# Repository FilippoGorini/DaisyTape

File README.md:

# DaisyTape

## Author

<!-- Insert Your Name Here -->

## Description

<!-- Describe your example here -->

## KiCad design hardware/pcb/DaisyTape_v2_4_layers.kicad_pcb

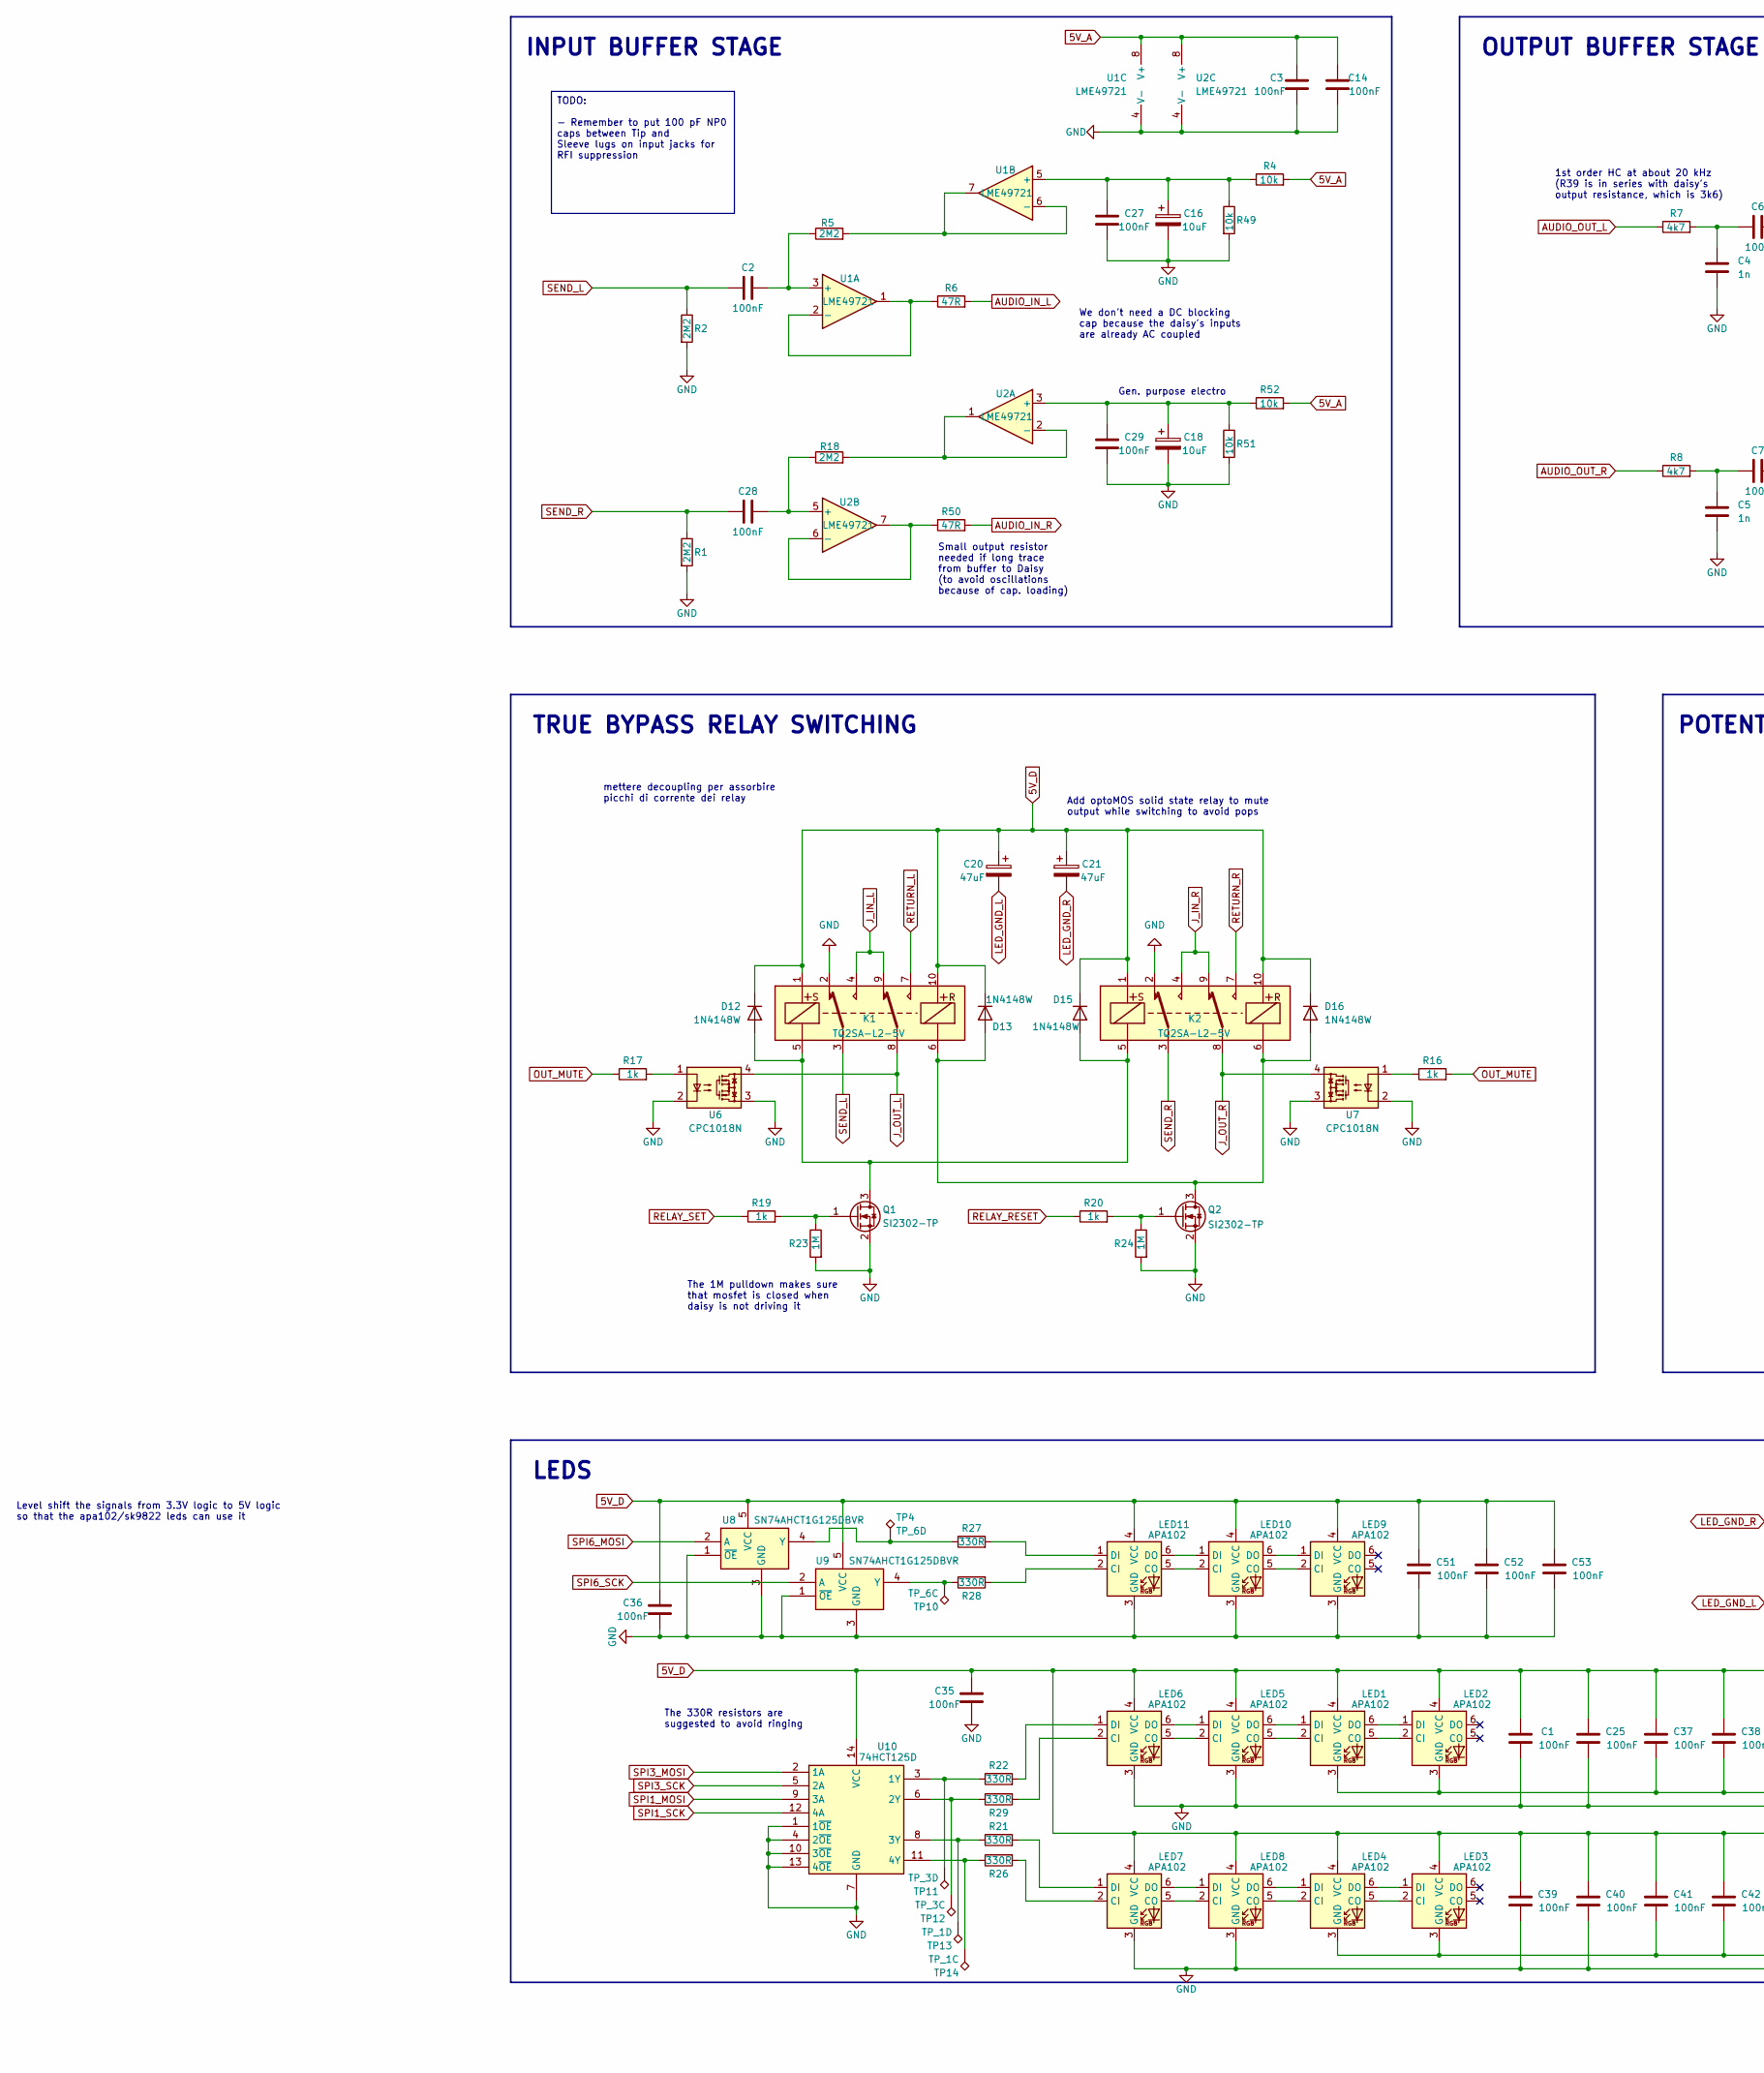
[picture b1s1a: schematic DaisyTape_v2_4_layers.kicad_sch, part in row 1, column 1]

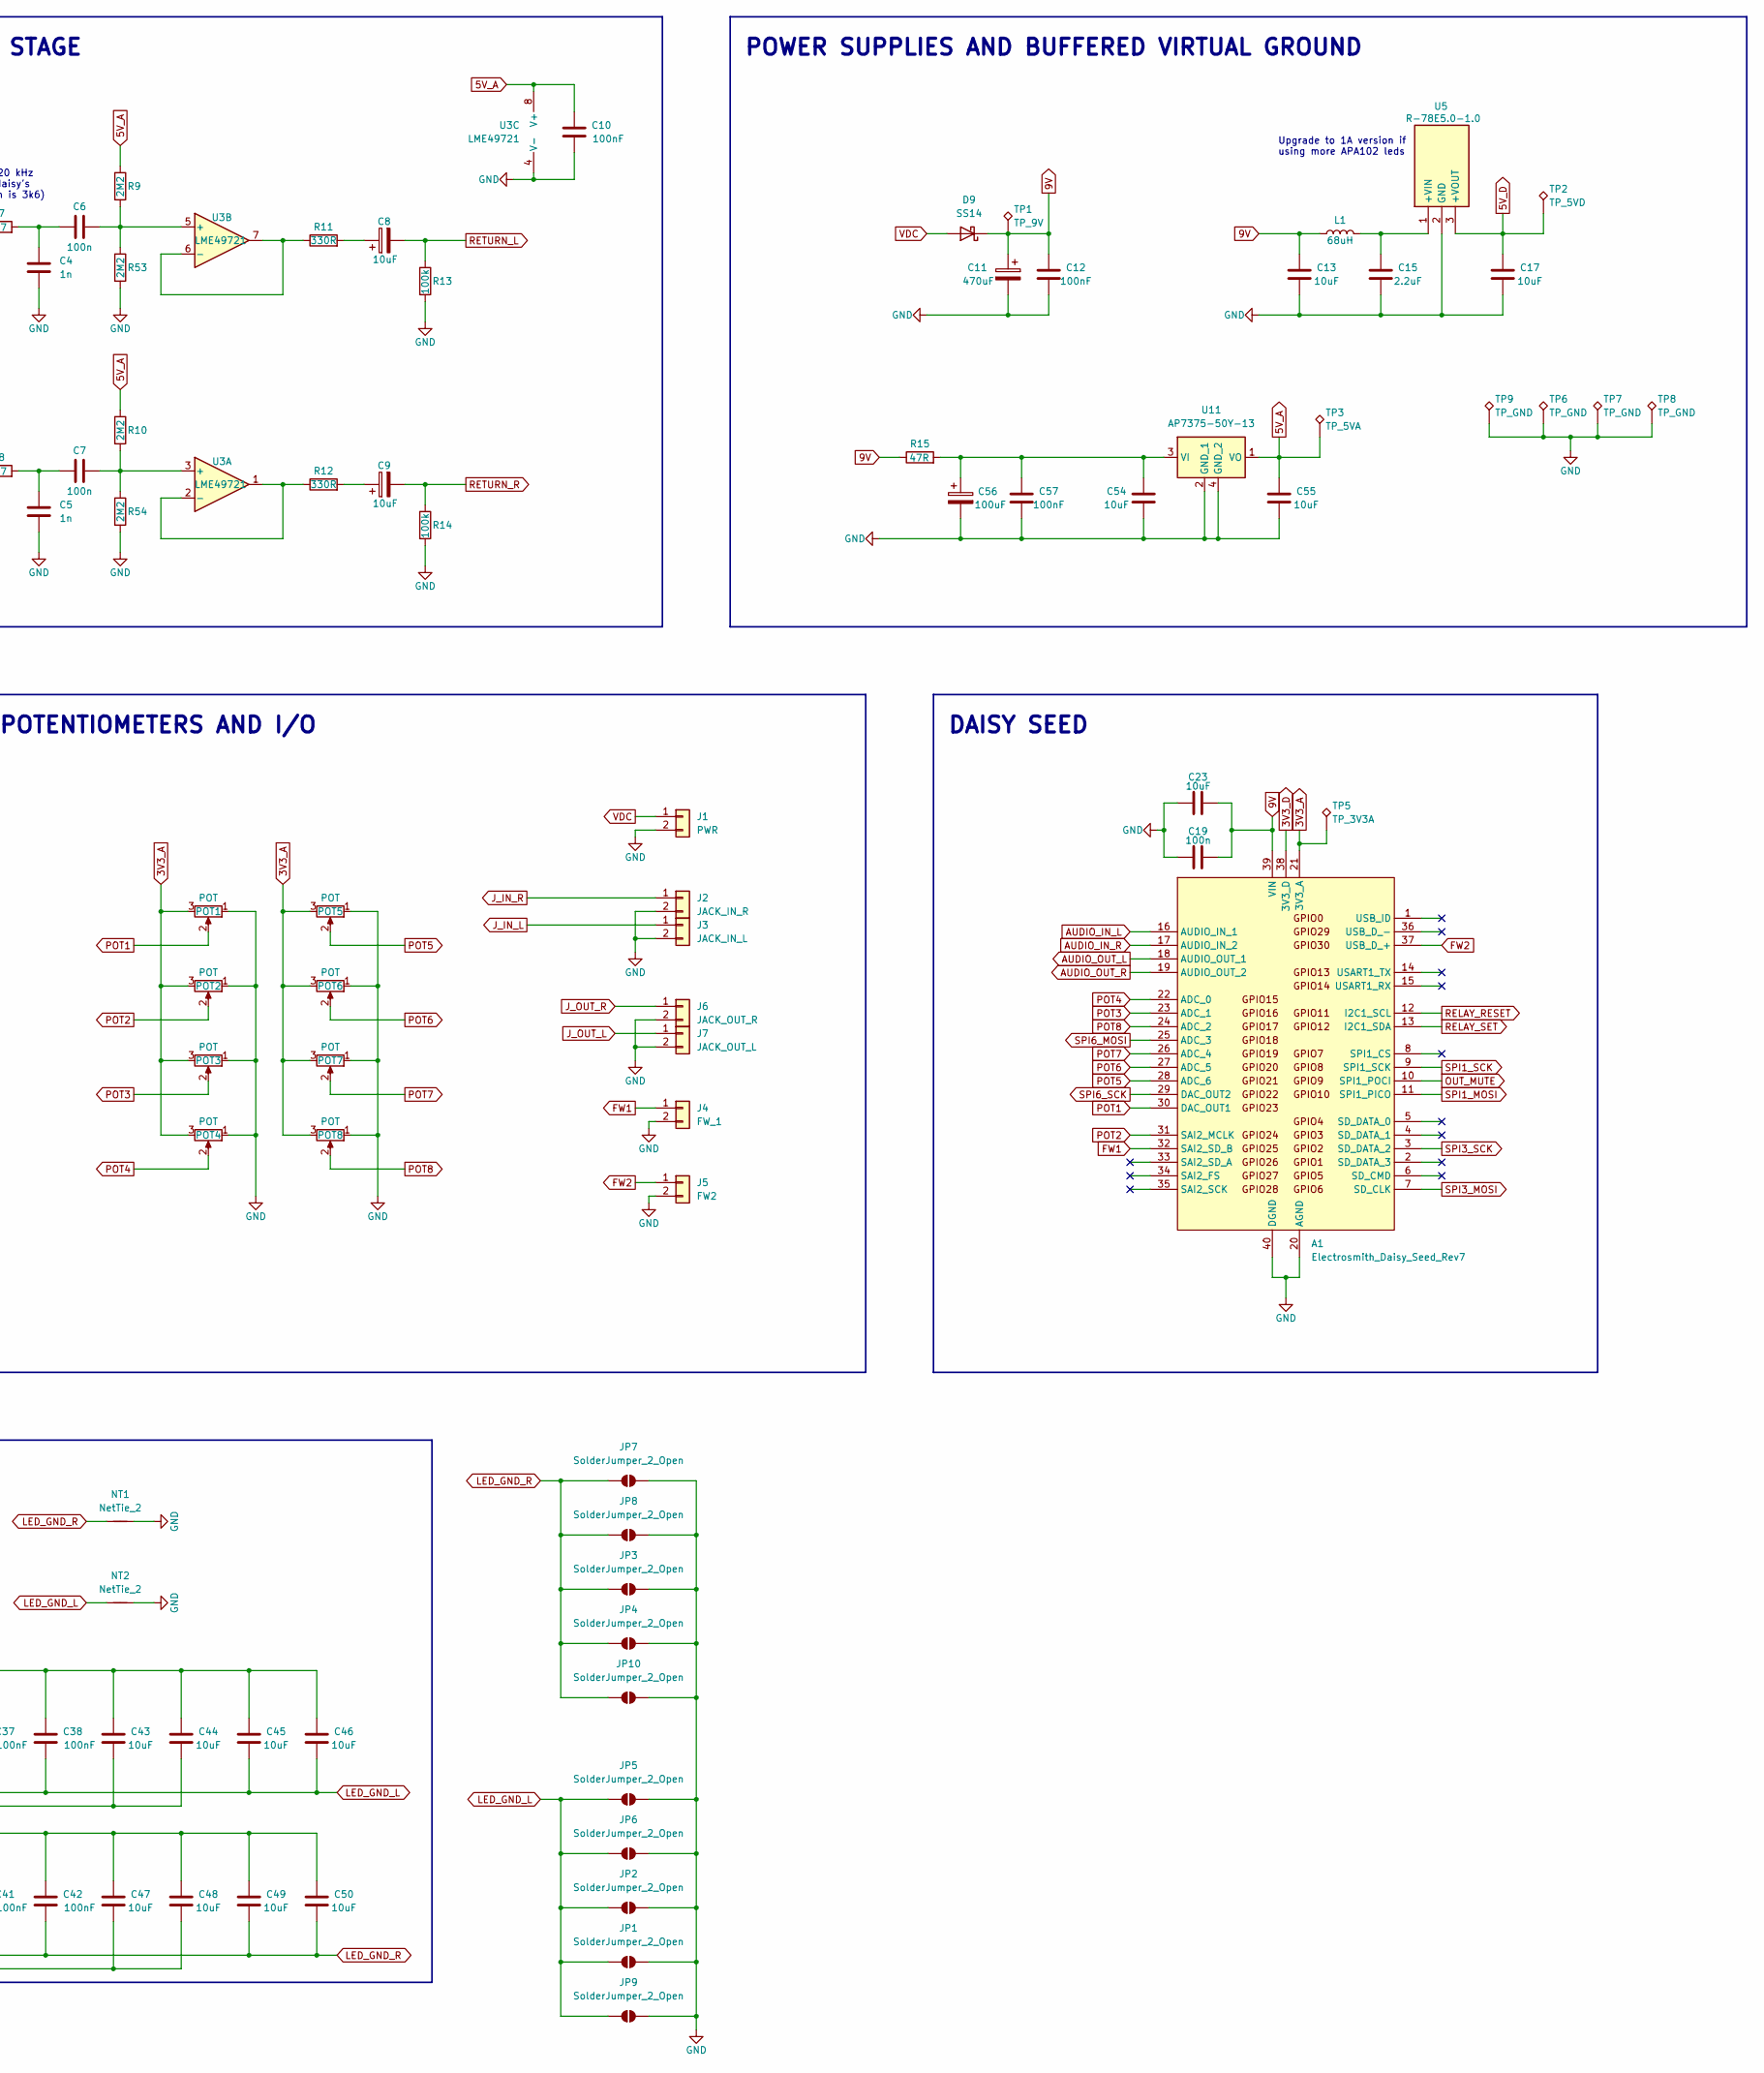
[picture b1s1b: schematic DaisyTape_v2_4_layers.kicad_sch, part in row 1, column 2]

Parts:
A1: Electrosmith_Daisy_Seed_Rev7; Electrosmith_Daisy_Seed
C1, C3, C10, C12, C14, C25, C35, C36, C37, C38, C39, C40, C41, C42, C51, C52, C53, C57: 100nF; C_0805_2012Metric_Pad1.18x1.45mm_HandSolder
C2, C27, C28, C29: 100nF; C_1206_3216Metric_Pad1.33x1.80mm_HandSolder
C4, C5: 1n; C_0805_2012Metric_Pad1.18x1.45mm_HandSolder
C6, C7: 100n; C_1206_3216Metric_Pad1.33x1.80mm_HandSolder
C8, C9, C16, C18: 10uF; CP_Elec_5x5.8
C11: 470uF; CP_Elec_8x10
C13, C17, C23, C43, C44, C45, C46, C47, C48, C49, C50, C54, C55: 10uF; C_1206_3216Metric_Pad1.33x1.80mm_HandSolder
C15: 2.2uF; C_1206_3216Metric_Pad1.33x1.80mm_HandSolder
C19: 100n; C_0805_2012Metric_Pad1.18x1.45mm_HandSolder
C20, C21: 47uF; CP_Elec_6.3x5.4
C56: 100uF; CP_Elec_6.3x7.7
D9: SS14; D_SMA
D12, D13, D15, D16: 1N4148W; D_SOD-123
J1: PWR; JST_PH_B2B-PH-K_1x02_P2.00mm_Vertical
J2: JACK_IN_R; JST_PH_B2B-PH-K_1x02_P2.00mm_Vertical
J3: JACK_IN_L; JST_PH_B2B-PH-K_1x02_P2.00mm_Vertical
J4: FW_1; JST_PH_B2B-PH-K_1x02_P2.00mm_Vertical
J5: FW2; JST_PH_B2B-PH-K_1x02_P2.00mm_Vertical
J6: JACK_OUT_R; JST_PH_B2B-PH-K_1x02_P2.00mm_Vertical
J7: JACK_OUT_L; JST_PH_B2B-PH-K_1x02_P2.00mm_Vertical
JP1, JP2, JP3, JP4, JP5, JP6, JP7, JP8, JP9, JP10: SolderJumper_2_Open; SolderJumper-2_P1.3mm_Open_RoundedPad1.0x1.5mm
K1, K2: TQ2SA-L2-5V; TQ2SA; Mouser Part Number 769-TQ2SA-L2-5V
L1: 68uH; SRR7045680M
LED1, LED2, LED3, LED4, LED5, LED6, LED7, LED8, LED9, LED10, LED11: APA102; LED_RGB_5050-6
NT1, NT2: NetTie_2; NetTie-2_SMD_Pad1.0mm
POT1, POT2, POT3, POT4, POT5, POT6, POT7, POT8: POT; Potentiometer_Alpha_RD901F-40-00D_Single_Vertical
Q1, Q2: SI2302-TP; SOT-23_Handsoldering; Mouser Part Number 833-SI2302-TP
R1, R2, R5, R18: 2M2; R_0805_2012Metric_Pad1.20x1.40mm_HandSolder; Tolerance 1 %; MPN AC0805FR-072M2L
R4, R49, R51, R52: 10k; R_0805_2012Metric_Pad1.20x1.40mm_HandSolder
R6, R15, R50: 47R; R_0805_2012Metric_Pad1.20x1.40mm_HandSolder
R7, R8: 4k7; R_0805_2012Metric_Pad1.20x1.40mm_HandSolder
R9, R10, R53, R54: 2M2; R_0805_2012Metric_Pad1.20x1.40mm_HandSolder
R11, R12, R21, R22, R26, R27, R28, R29: 330R; R_0805_2012Metric_Pad1.20x1.40mm_HandSolder
R13, R14: 100k; R_0805_2012Metric_Pad1.20x1.40mm_HandSolder
R16, R17, R19, R20: 1k; R_0805_2012Metric_Pad1.20x1.40mm_HandSolder
R23, R24: 1M; R_0805_2012Metric_Pad1.20x1.40mm_HandSolder
TP1: TP_9V; TestPoint_Pad_D1.0mm
TP2: TP_5VD; TestPoint_Pad_D1.0mm
TP3: TP_5VA; TestPoint_Pad_D1.0mm
TP4: TP_6D; TestPoint_Pad_D1.0mm
TP5: TP_3V3A; TestPoint_Pad_D1.0mm
TP6, TP7, TP8, TP9: TP_GND; TestPoint_THTPad_D2.0mm_Drill1.0mm_CUSTOM
TP10: TP_6C; TestPoint_Pad_D1.0mm
TP11: TP_3D; TestPoint_Pad_D1.0mm
TP12: TP_3C; TestPoint_Pad_D1.0mm
TP13: TP_1D; TestPoint_Pad_D1.0mm
TP14: TP_1C; TestPoint_Pad_D1.0mm
U1, U2, U3: LME49721; SOIC-8_3.9x4.9mm_P1.27mm
U5: R-78E5.0-1.0; R78E5010; Mouser Part Number 919-R-78E5.0-1.0
U6, U7: CPC1018N; SOP-4_3.8x4.1mm_P2.54mm
U8, U9: SN74AHCT1G125DBVR; SOT-23-5_HandSoldering; Mouser Part Number 595-SNAHCT1G125DBVR
U10: 74HCT125D; SOIC-14_3.9x8.7mm_P1.27mm; Mouser Part Number 771-74HCT125D-T
U11: AP7375-50Y-13; SOT-89-3_Handsoldering; Mouser Part Number 621-AP7375-50Y-13

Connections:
3V3_A: A1.21 (3V3_A), POT1.3, POT2.3, POT3.3, POT4.3, POT5.3, POT6.3, POT7.3, POT8.3, TP5.1
3V3_D: A1.38 (3V3_D)
5V_A: C3.2, C10.2, C14.2, C55.2, R4.2, R9.1, R10.1, R52.2, TP3.1, U1.8 (V+), U2.8 (V+), U3.8 (V+), U11.1 (VO)
5V_D: C1.2, C17.2, C20.1, C21.1, C25.2, C35.2, C36.2, C37.2, C38.2, C39.2, C40.2, C41.2, C42.2, C43.2, C44.2, C45.2, C46.2, C47.2, C48.2, C49.2, C50.2, C51.2, C52.2, C53.2, D12.1 (K), D13.1 (K), D15.1 (K), D16.1 (K), K1.1, K1.10, K2.1, K2.10, LED1.4 (VCC), LED2.4 (VCC), LED3.4 (VCC), LED4.4 (VCC), LED5.4 (VCC), LED6.4 (VCC), LED7.4 (VCC), LED8.4 (VCC), LED9.4 (VCC), LED10.4 (VCC), LED11.4 (VCC), TP2.1, U5.3 (+VOUT), U8.5 (VCC), U9.5 (VCC), U10.14 (VCC)
9V: A1.39 (VIN), C11.1, C12.2, C13.2, C19.2, C23.2, D9.1 (K), L1.1, R15.1, TP1.1
AUDIO_IN_L: A1.16 (AUDIO_IN_1), R6.2
AUDIO_IN_R: A1.17 (AUDIO_IN_2), R50.2
AUDIO_OUT_L: A1.18 (AUDIO_OUT_1), R7.1
AUDIO_OUT_R: A1.19 (AUDIO_OUT_2), R8.1
FW1: A1.32 (SAI2_SD_B), J4.1
FW2: A1.37 (USB_D_+), J5.1
GND: A1.20 (AGND), A1.40 (DGND), C1.1, C3.1, C4.1, C5.1, C10.1, C11.2, C12.1, C13.1, C14.1, C15.1, C16.2, C17.1, C18.2, C19.1, C23.1, C25.1, C27.1, C29.1, C35.1, C36.1, C39.1, C40.1, C43.1, C44.1, C47.1, C48.1, C51.1, C52.1, C53.1, C54.1, C55.1, C56.2, C57.1, J1.2, J2.2, J3.2, J4.2, J5.2, J6.2, J7.2, JP1.2 (B), JP2.2 (B), JP3.2 (B), JP4.2 (B), JP5.2 (B), JP6.2 (B), JP7.2 (B), JP8.2 (B), JP9.2 (B), JP10.2 (B), K1.2, K2.2, LED5.3 (GND), LED6.3 (GND), LED7.3 (GND), LED8.3 (GND), LED9.3 (GND), LED10.3 (GND), LED11.3 (GND), NT1.2, NT2.2, POT1.1, POT2.1, POT3.1, POT4.1, POT5.1, POT6.1, POT7.1, POT8.1, Q1.2 (S), Q2.2 (S), R1.2, R2.2, R13.2, R14.2, R23.2, R24.2, R49.2, R51.2, R53.2, R54.2, TP6.1, TP7.1, TP8.1, TP9.1, U1.4 (V-), U2.4 (V-), U3.4 (V-), U5.2 (GND), U6.2, U6.3, U7.2, U7.3, U8.1 (~OE), U8.3 (GND), U9.1 (~OE), U9.3 (GND), U10.1 (1~OE), U10.4 (2~OE), U10.7 (GND), U10.10 (3~OE), U10.13 (4~OE), U11.2 (GND_1), U11.4 (GND_2)
J_IN_L: J3.1, K1.4, K1.9
J_IN_R: J2.1, K2.4, K2.9
J_OUT_L: J7.1, K1.8, U6.4
J_OUT_R: J6.1, K2.8, U7.4
LED_GND_L: C20.2, C37.1, C38.1, C45.1, C46.1, JP1.1 (A), JP2.1 (A), JP5.1 (A), JP6.1 (A), JP9.1 (A), LED1.3 (GND), LED2.3 (GND), NT2.1
LED_GND_R: C21.2, C41.1, C42.1, C49.1, C50.1, JP3.1 (A), JP4.1 (A), JP7.1 (A), JP8.1 (A), JP10.1 (A), LED3.3 (GND), LED4.3 (GND), NT1.1
unnamed: C4.2, C6.1, R7.2
unnamed: C5.2, C7.1, R8.2
unnamed: C8.1, R11.2
unnamed: C9.1, R12.2
unnamed: D12.2 (A), D15.2 (A), K1.5, K2.5, Q1.3 (D)
unnamed: D13.2 (A), D16.2 (A), K1.6, K2.6, Q2.3 (D)
unnamed: LED1.2 (CI), LED5.5 (CO)
unnamed: LED1.5 (CO), LED2.2 (CI)
unnamed: LED1.1 (DI), LED5.6 (DO)
unnamed: LED1.6 (DO), LED2.1 (DI)
unnamed: LED3.2 (CI), LED4.5 (CO)
unnamed: LED3.1 (DI), LED4.6 (DO)
unnamed: LED4.2 (CI), LED8.5 (CO)
unnamed: LED4.1 (DI), LED8.6 (DO)
unnamed: LED5.2 (CI), LED6.5 (CO)
unnamed: LED5.1 (DI), LED6.6 (DO)
unnamed: LED6.2 (CI), R29.2
unnamed: LED6.1 (DI), R22.2
unnamed: LED7.2 (CI), R26.2
unnamed: LED7.5 (CO), LED8.2 (CI)
unnamed: LED7.1 (DI), R21.2
unnamed: LED7.6 (DO), LED8.1 (DI)
unnamed: LED10.2 (CI), LED11.5 (CO)
unnamed: LED9.2 (CI), LED10.5 (CO)
unnamed: LED10.1 (DI), LED11.6 (DO)
unnamed: LED9.1 (DI), LED10.6 (DO)
unnamed: LED11.2 (CI), R28.2
unnamed: LED11.1 (DI), R27.2
unnamed: Q1.1 (G), R19.2, R23.1
unnamed: Q2.1 (G), R20.2, R24.1
unnamed: R16.1, U7.1
unnamed: R17.2, U6.1
unnamed: C2.2, R5.1, U1.3 (+)
unnamed: R6.1, U1.1, U1.2 (-)
unnamed: C16.1, C27.2, R4.1, R49.1, U1.5 (+)
unnamed: R5.2, U1.6 (-), U1.7
unnamed: C18.1, C29.2, R51.1, R52.1, U2.3 (+)
unnamed: R18.2, U2.1, U2.2 (-)
unnamed: C28.2, R18.1, U2.5 (+)
unnamed: R50.1, U2.6 (-), U2.7
unnamed: C7.2, R10.2, R54.1, U3.3 (+)
unnamed: R12.1, U3.1, U3.2 (-)
unnamed: C6.2, R9.2, R53.1, U3.5 (+)
unnamed: R11.1, U3.6 (-), U3.7
unnamed: C15.2, L1.2, U5.1 (+VIN)
unnamed: R27.1, TP4.1, U8.4 (Y)
unnamed: R28.1, TP10.1, U9.4 (Y)
unnamed: R22.1, TP11.1, U10.3 (1Y)
unnamed: R29.1, TP12.1, U10.6 (2Y)
unnamed: R21.1, TP13.1, U10.8 (3Y)
unnamed: R26.1, TP14.1, U10.11 (4Y)
unnamed: C54.2, C56.1, C57.2, R15.2, U11.3 (VI)
OUT_MUTE: A1.10 (SPI1_POCI), R16.2, R17.1
POT1: A1.30 (DAC_OUT1), POT1.2
POT2: A1.31 (SAI2_MCLK), POT2.2
POT3: A1.23 (ADC_1), POT3.2
POT4: A1.22 (ADC_0), POT4.2
POT5: A1.28 (ADC_6), POT5.2
POT6: A1.27 (ADC_5), POT6.2
POT7: A1.26 (ADC_4), POT7.2
POT8: A1.24 (ADC_2), POT8.2
RELAY_RESET: A1.12 (I2C1_SCL), R20.1
RELAY_SET: A1.13 (I2C1_SDA), R19.1
RETURN_L: C8.2, K1.7, R13.1
RETURN_R: C9.2, K2.7, R14.1
SEND_L: C2.1, K1.3, R2.1
SEND_R: C28.1, K2.3, R1.1
SPI1_MOSI: A1.11 (SPI1_PICO), U10.9 (3A)
SPI1_SCK: A1.9 (SPI1_SCK), U10.12 (4A)
SPI3_MOSI: A1.7 (SD_CLK), U10.2 (1A)
SPI3_SCK: A1.3 (SD_DATA_2), U10.5 (2A)
SPI6_MOSI: A1.25 (ADC_3), U8.2 (A)
SPI6_SCK: A1.29 (DAC_OUT2), U9.2 (A)
VDC: D9.2 (A), J1.1

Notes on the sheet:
POWER SUPPLIES AND BUFFERED VIRTUAL GROUND
The 330R resistors are suggested to avoid ringing
The 1M pulldown makes sure that mosfet is closed when daisy is not driving it
LEDS
Level shift the signals from 3.3V logic to 5V logic so that the apa102/sk9822 leds can use it
INPUT BUFFER STAGE
mettere decoupling per assorbire picchi di corrente dei relay
DAISY SEED
POTENTIOMETERS AND I/O
TRUE BYPASS RELAY SWITCHING
We don't need a DC blocking cap because the daisy's inputs are already AC coupled
Small output resistor needed if long trace from buffer to Daisy (to avoid oscillations because of cap. loading)
Upgrade to 1A version if using more APA102 leds
OUTPUT BUFFER STAGE
Add optoMOS solid state relay to mute output while switching to avoid pops
Gen. purpose electro
1st order HC at about 20 kHz (R39 is in series with daisy's output resistance, which is 3k6)
TODO: - Remember to put 100 pF NP0 caps between Tip and Sleeve lugs on input jacks for RFI suppression

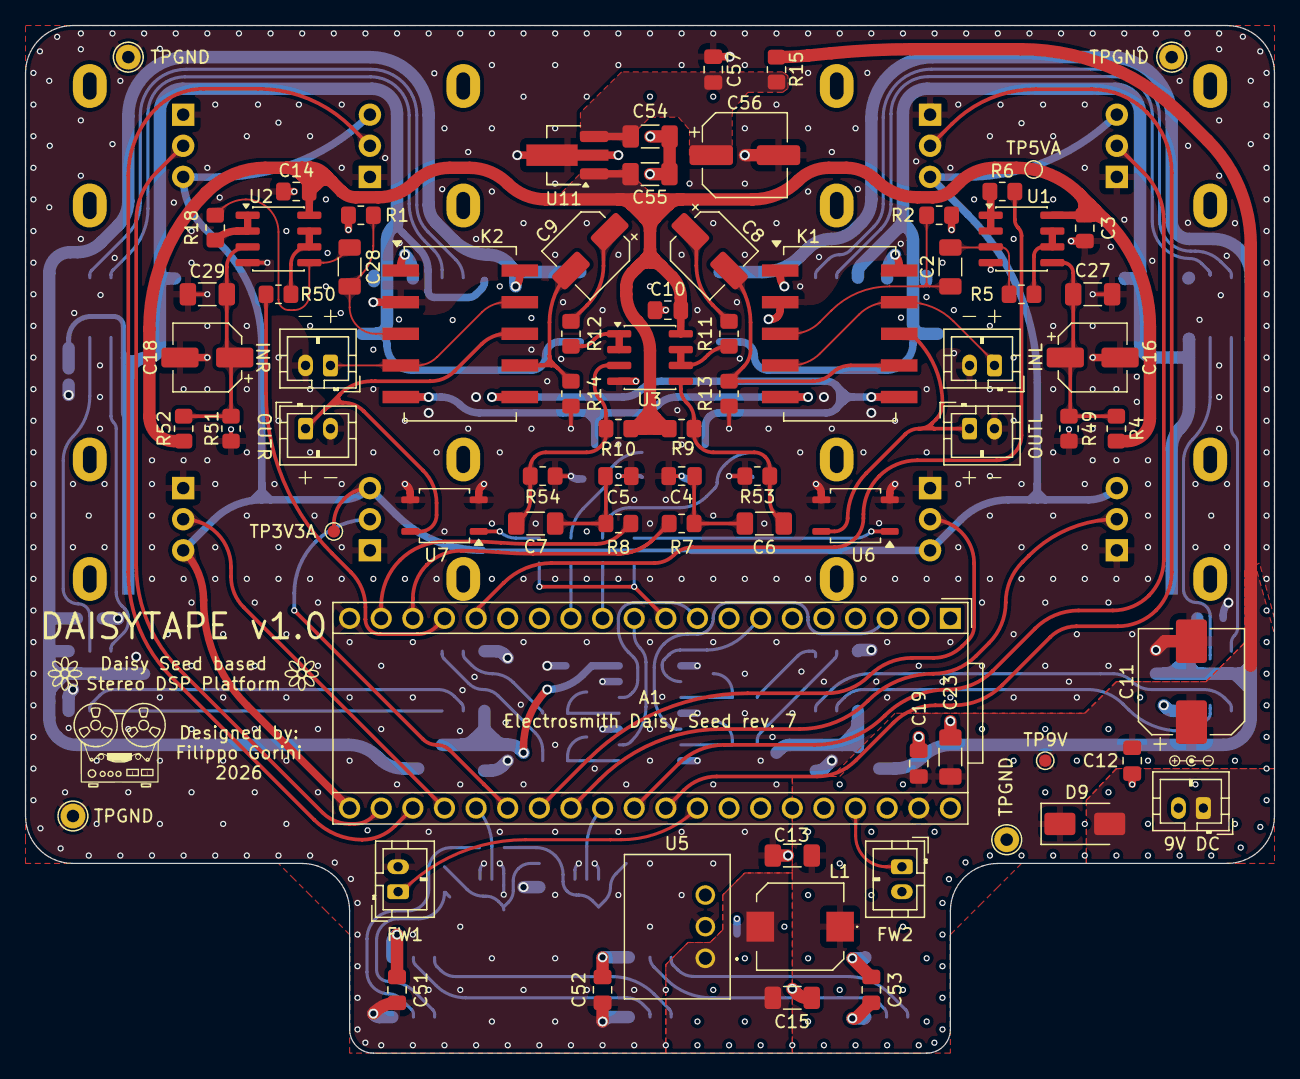
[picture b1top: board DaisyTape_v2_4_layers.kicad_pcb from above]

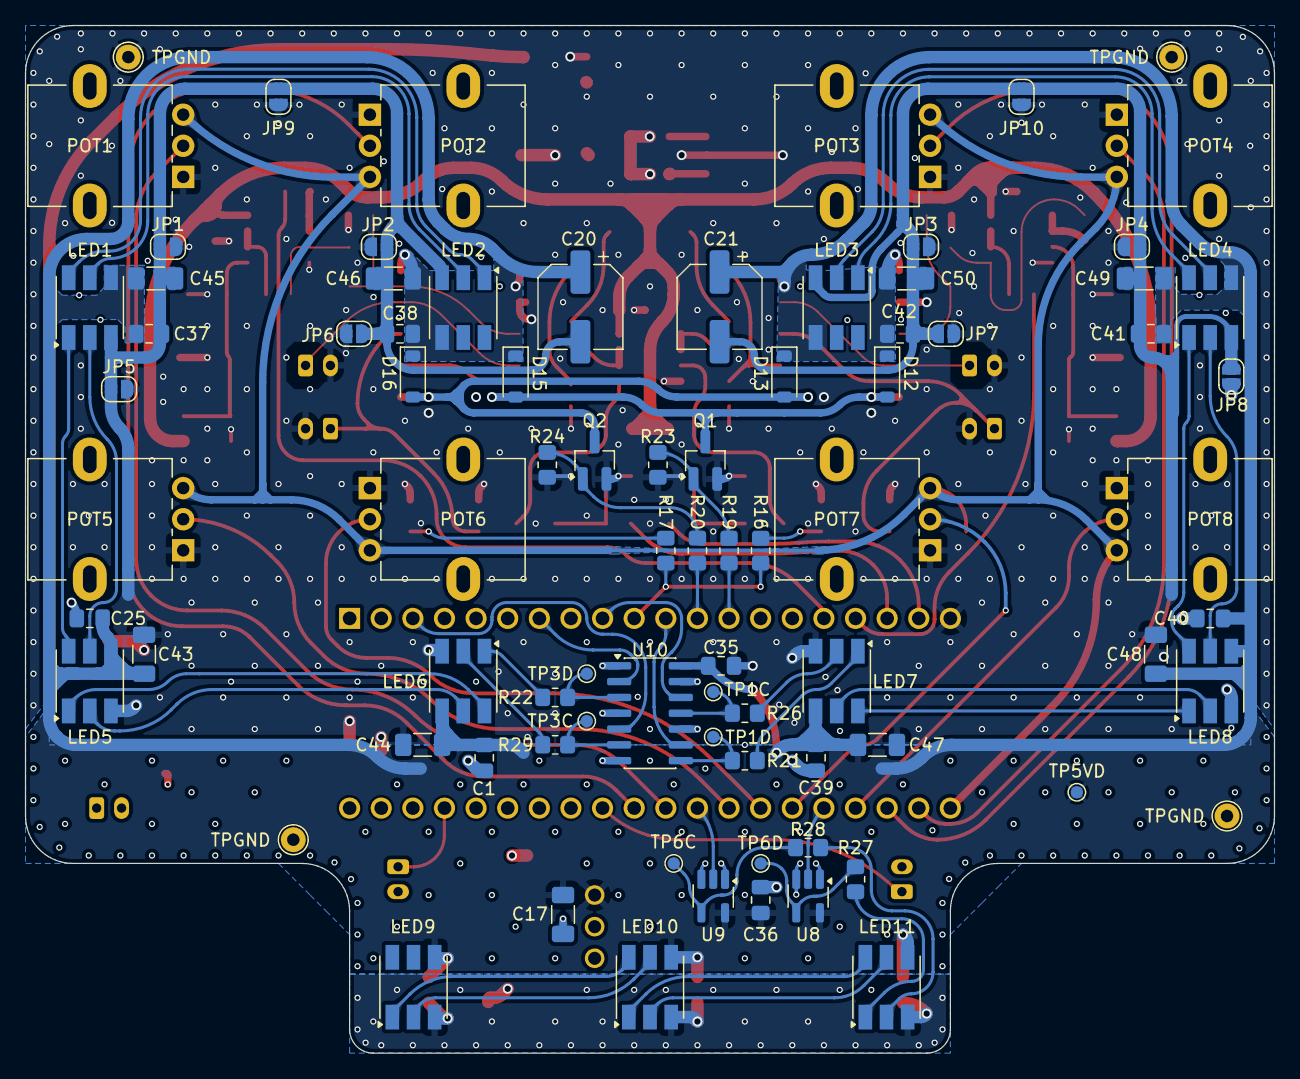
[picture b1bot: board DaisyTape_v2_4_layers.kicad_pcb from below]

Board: 4 copper layers, 100.3 x 82.5 mm, 155 parts (80 on the bottom side), 91 nets.

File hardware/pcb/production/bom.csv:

Designator,Footprint,Quantity,Value,LCSC Part #
A1,Electrosmith_Daisy_Seed,1,Electrosmith_Daisy_Seed_Rev7,
"C1, C10, C12, C14, C25, C3, C35, C36, C37, C38, C39, C40, C41, C42, C51, C52, C53, C57",0805,18,100nF,
C11,CP_Elec_8x10,1,470uF,
"C13, C17, C23, C43, C44, C45, C46, C47, C48, C49, C50, C54, C55",1206,13,10uF,
C15,1206,1,2.2uF,
"C16, C18, C8, C9",CP_Elec_5x5.8,4,10uF,
C19,0805,1,100n,
"C2, C27, C28, C29",1206,4,100nF,
"C20, C21",CP_Elec_6.3x5.4,2,47uF,
"C4, C5",0805,2,1n,
C56,CP_Elec_6.3x7.7,1,100uF,
"C6, C7",1206,2,100n,
"D1, D17, D18, D19, D2, D3, D4, D5, D6, D7, D8",LED_RGB_5050-6,11,APA102,
"D12, D13, D15, D16",D_SOD-123,4,1N4148W,
D9,D_SMA,1,SS14,
J1,JST_PH_B2B-PH-K_1x02_P2.00mm_Vertical,1,PWR,
J2,JST_PH_B2B-PH-K_1x02_P2.00mm_Vertical,1,JACK_IN_R,
J3,JST_PH_B2B-PH-K_1x02_P2.00mm_Vertical,1,JACK_IN_L,
J4,JST_PH_B2B-PH-K_1x02_P2.00mm_Vertical,1,FW_1,
J5,JST_PH_B2B-PH-K_1x02_P2.00mm_Vertical,1,FW2,
J6,JST_PH_B2B-PH-K_1x02_P2.00mm_Vertical,1,JACK_OUT_R,
J7,JST_PH_B2B-PH-K_1x02_P2.00mm_Vertical,1,JACK_OUT_L,
"K1, K2",TQ2SA,2,TQ2SA-L2-5V,
L1,SRR7045680M,1,68uH,
"POT1, POT2, POT3, POT4, POT5, POT6, POT7, POT8",Potentiometer_Alpha_RD901F-40-00D_Single_Vertical,8,POT,
"Q1, Q2",SOT-23_Handsoldering,2,SI2302-TP,
"R1, R18, R2, R5",0805,4,2M2,AC0805FR-072M2L
"R10, R53, R54, R9",0805,4,2M2,
"R11, R12, R21, R22, R26, R27, R28, R29",0805,8,330R,
"R13, R14",0805,2,100k,
"R15, R50, R6",0805,3,47R,
"R16, R17, R19, R20",0805,4,1k,
"R23, R24",0805,2,1M,
"R4, R49, R51, R52",0805,4,10k,
"R7, R8",0805,2,4k7,
"U1, U2, U3",SOIC-8_3.9x4.9mm_P1.27mm,3,LME49721,
U10,SOIC-14_3.9x8.7mm_P1.27mm,1,74HCT125D,
U11,SOT-89-3_Handsoldering,1,AP7375-50Y-13,
U5,R78E5010,1,R-78E5.0-1.0,
"U6, U7",SOP-4_3.8x4.1mm_P2.54mm,2,CPC1018N,
"U8, U9",SOT-23-5_HandSoldering,2,SN74AHCT1G125DBVR,

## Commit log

2025-11-18 InputFilters class ported and working
    - Succesfully ported Linkwitz-Riley, DaisyInputFilters, and TapeProcessor classes
    - New project structure with separate include and src directories
    - Input filters now working correctly
    ISSUES:
    - When moving the pots too fast there are audible artifacts, maybe we need smoothing or a different rate?
    - We can't yet test the wet dry mix and the makeup until we know how much the needed delay is
2025-11-19 Slight refactor, new updateParams() method, new TapeParams structure
    - Moved params structure inside of TapeProcessor and added updateParams() method
    - Slight refactor of main loop to read pots, update params, log status separately
    ISSUES:
    - When moving the pots too fast there are audible artifacts, maybe we need smoothing or a different rate? UPDATE: higher rate helps slightly but the problem remains
    - We can't yet test the wet dry mix and the makeup until we know how much the needed delay is
    TODO:
2025-11-24 Added loss filter processing, azimuth yet to fix
    - Added DaisyLossFilter and DaisyAzimuthProc classes (Azimuth has problems so it is not used yet)
    - Added the loss filter processing in the TapeProcessor class
    - Implemented the logging at a slower rate wrt parameter updates
    ISSUES:
    - The azimuth processing is behaving strangely (additional delayed sound at a lower volume)
    - When moving the pots too fast there are audible artifacts, maybe we need smoothing or a different rate? UPDATE: higher rate helps slightly but the problem remains
2025-11-24 Improvements to the DaisyLossFilter class (RBJ head-bump filter, increased FIR order)
    - Improved DaisyLossFilter by using RBJ implementation as the original JUCE code did instead of the naive biquad formula
    - Increased loss filter FIR filter order to 70 to better match the spectral bins size of the original implementation running at 44.1 kHz
    - Added matlab script to compare the coefficients of the two implementations
    ISSUES:
    - Sometimes the audio cuts out and totally glitches out, not sure if hardware problem or a loss filter software issue
    - The azimuth processing is behaving strangely (additional delayed sound at a lower volume)
2025-11-24 Updated project to use the latest versions of libDaisy and DaisySP
2025-11-24 Also fixed the c_cpp_properties with the new libraries correct path
2025-11-24 Added DaisyDegrade processor
    - Added DaisyDegrade class, which seems to behave as expected but is not really convincing, gotta compare more in depth with original code
    ISSUES:
    - There seems to be some non predicatability given by the Degrade class which causes rare audio callback underruns
    - We're getting close to the flash memory limit
    - Sometimes the audio cuts out and totally glitches out, not sure if hardware problem or a loss filter software issue
    - The azimuth processing is behaving strangely (additional delayed sound at a lower volume)
2025-11-25 DaisyDegrade class improvements to increase accuracy wrt original implementation and reduce CPU load
    - Modified the DaisyDegrade class to use similar logic to JUCE's Random and SmoothedValue classes
    - This also seems to give more predictability, as now the average CPU load is 24% and the max is 44%, compared to the previous peaks of 96%
    - Ported JuceRandom, LinSmoothed, MulSmoothed and ChowLevelDetector from JUCE and chowdsp libraries
    ISSUES:
    - We're getting close to the flash memory limit
    - Sometimes the audio cuts out and totally glitches out, not sure if hardware problem or a loss filter software issue
2025-11-25 Just fixed vscode warning by adding an std:: somewhere, not really needed though
2025-12-02 Updated main to use all 8 knobs instead of 4, discovered possible cause of glitches
    ISSUES:
    - CRITICAL: the updateParams can be interrupted by the audio callback, this causes incoherent parameter sets which could trigger IIR instabilities, this could be the cause of the destructive audio gl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
    - We're getting close to the flash memory limit
    - Sometimes the audio cuts out and totally glitches out, not sure if hardware problem or a loss filter software issue (probable IIR instability at this point)
    - The azimuth processing is behaving strangely (additional delayed sound at a lower volume)
    - When moving the pots too fast there are audible artifacts, maybe we need smoothing
2026-03-07 Moved program to SRAM, added PCB project
2026-05-05 Updated c_cpp_properties.json with linux configuration, deleted useless backups
2026-05-05 Refactored all critical classes to prepareParams() in main thread and applyParams() in the audio callback, maybe problem fixed?
    DONE:
    - Refactored all critical classes: now the parameters are prepared in main thread but applied inside of a single audio callback only once they're ready
    ISSUES:
    - We're getting close to the flash memory limit
    - The azimuth processing is behaving strangely (additional delayed sound at a lower volume)
    - When moving the pots too fast there are audible artifacts, maybe we need smoothing or a different rate? UPDATE: higher rate helps slightly but the problem remains. Regarding this, maybe let's check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
